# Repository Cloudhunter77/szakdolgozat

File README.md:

# ModuNode – moduláris okosotthon platform

Szakdolgozat: moduláris okosotthon node-ok ESP32-C6 mikrovezérlőn. A végleges irány Matter (over Thread)
Home Assistanttal; a köztes lépések ESPHome-on készültek.

## Szerkezet
| Mappa | Tartalom | Állapot |
|---|---|---|
| [`firmware/esphome-demo/`](firmware/esphome-demo/) | ESPHome vezérlő demó: relé, ajtóérzékelő, Kézi/Automata mód, webes felület | ✅ hardveren tesztelve |
| [`firmware/matter-c6/`](firmware/matter-c6/) | ESP-Matter alapú firmware, Matter over Thread, Home Assistant | ✅ párosítva HA-ba (cp-02) |
| [`docs/`](docs/) | Tervek, jegyzetek | |

A tesztelt, visszaállítható állapotok listája: [`CHECKPOINTS.md`](CHECKPOINTS.md).

## Eszközök
- Hardver: ESP32-C6 (DevKitC-1 / Super Mini), Home Assistant + Thread border router
- ESPHome (Python venv), ESP-IDF v5.5.5 + `espressif/esp_matter` komponens
- Fejlesztői gép: Linux Mint

Az egyes alprojektek indítása a saját `README.md`-jükben van.

## Titkok
A WiFi jelszavak és kulcsok a `secrets.yaml` fájlokban vannak, ezek **nincsenek** a repóban.
Új gépen a `secrets.example.yaml`-ből kell létrehozni őket.

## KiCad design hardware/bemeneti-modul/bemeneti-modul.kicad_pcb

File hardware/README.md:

# Hardver – KiCad 10 projektek

Specifikációk: `docs/kontextus/MODULMAG-SPEC.md`, `docs/kontextus/VEZERLO-SPEC.md`; ütemterv: `docs/kontextus/UTEMTERV.md`.

| Mappa | Mi |
|---|---|
| `lib/` | közös saját könyvtár: `modularis.kicad_sym`, `modularis.pretty/`, `3d/` |
| `modulmag/` | a modulmag **egyetlen** kapcsolási lapja; a három modul hierarchikus lapként használja (`../modulmag/modulmag.kicad_sch`), a saját projektje csak az önálló ellenőrzéshez kell |
| `vezerlo/` | ESP32-C6 vezérlő |
| `led-modul/`, `rele-modul/`, `bemeneti-modul/` | a modulok (modulmag + a saját részük) |
| `gen/` | a vázlatok generátora: `gen/build.sh <lap>` → `<lap>.py` → `.kicad_sch` + ERC, netlista, PDF az `out/`-ba. **Felülírja a kézi elrendezést** – elrendezés után már csak kézzel módosítsd a lapot |

Laponként külön projekt = külön NYÁK, külön gerber. A modulmagot csak egy helyen kell javítani.

Ellenőrzés (Claude Code futtatja): `kicad-cli` (Flatpak: `flatpak run --command=kicad-cli org.kicad.KiCad`) –
ERC, netlista-export és összevetés a specifikációval, később DRC és gerber.

## Munkafolyamat (D67)

- **Forrás:** amíg Balázs egy lapot nem szerkeszt kézzel, a `gen/<lap>.py` a forrás. Amint kézzel átrendez rajta
  valamit, onnantól a `.kicad_sch` – arra a lapra a generátort **nem futtatjuk újra** (a mozgatások elvesznének).
  A kézzel átvett lapok: **mind az öt (2026-10-23)** – `gen/kezi-lapok.txt`; a `build.sh` ezeket nem generálja újra, csak
  ellenőrzi (ERC, netlista, PDF). Módosítás innentől a `.kicad_sch`-ban (KiCad-ben vagy MCP-vel), nem a `gen/<lap>.py`-ban.
- **Egyszerre csak egyikünk szerkeszt:** Balázs ment → Claude módosít (fájlban vagy KiCad MCP-vel) → Balázs a
  KiCad-ben újratölti a lapot (File → Revert).
- **Minden módosítás után:**
  - `gen/build.sh <lap>` (csak generátoros lapnál) – ERC-t is futtat, `Found 0 violations` kell
    (a `modulmag` önállóan ~55 jelzést ad a lógó hierarchikus lábak miatt – ez rendben van, a modulok ERC-je a mérvadó)
  - netlista-összevetés: `kicad-cli sch export netlist -o out/<lap>.net <lap>/<lap>.kicad_sch`, majd
    `python3 -I gen/netcmp.py out/<lap>.before.net out/<lap>.net` – a bekötés változatlan, ha 0 / 0 eltérés
    (relé és LED: 4 várt eltérés a D6/JP2 buszos táp opció miatt). Az `out/` gitignore-ban van, a `.before.net`
    csak helyben létezik; szándékos bekötés-változás után újra kell menteni.
  - vizuális ellenőrzés: KiCad MCP `sch_visual_qa` – a „symbol_overlap” többnyire formai (tápszimbólum a láb végén,
    szomszédos alkatrész, többegységes U9), ezért PDF → PNG kivágáson is megnézni.
- **KiCad MCP:** `kicad-mcp-pro` (uvx, Python 3.13), helyi scope, munkaterület = `hardware/`, **írható mód**
  (`KICAD_MCP_OPERATING_MODE=write`). Minden projektmappában `output/` munkamappát hoz létre (gitignore-ban).

**Fő áramutak (`gen/aramut.py`, D91):** `flatpak run --command=python3 org.kicad.KiCad gen/aramut.py <lap>` – a DRC-ben a táp-sávok
minimuma csak 0,2 mm (mellékágak), ezért ez nézi, hogy a fő út (pl. betáp → biztosíték → sorkapocs, FET → sönt, busz) a keskenyebb
sávok nélkül is egyben van-e; az `ellenorzes.py` 6. lépése futtatja.

**Rajzszerkesztés szkriptből (`gen/schedit.py`, D90):** a kézi `.kicad_sch`-okhoz – szimbólumok és lábpozíciók (a forgatás /
tükrözés a `kigen` szerint), vezeték, címke, tápszimbólum (a hálózat neve a Value), PWR_FLAG, törlés, áthelyezés, címke csonkra
(`stub_labels`), a D-hivatkozások kivétele a konzulensnek szánt szövegekből (`strip_d`). A `save()` csak akkor ír, ha a fájl a beolvasás
óta nem változott (Balázs nem mentett közben). Minden módosítás után: netlista-összevetés (`gen/netcmp.py`) + ERC + SVG-kép.

## STM32CubeMX-projektek (`cubemx/`)
`python3 gen/cubemx.py` → `cubemx/<modul>/<modul>.ioc` a MODULMAG-SPEC 7. fejezetének lábkiosztásából (a jel- és
üzemmódnevek a CubeMX 6.18 adatbázisából). MCU: **STM32L433RCT3** (D78). Indítás: `flatpak run com.st.STM32CubeMX` →
File → Load Project. A pinout nézet a lábhozzárendelést ellenőrzi; a belső kapcsolatokat (COMP2 → TIM1/TIM15/TIM16 BKIN,
DAC1_OUT1 → COMP2 INM, ADC1_IN8 + COMP2_INP a PA3-on) a CubeMX-ben kézzel kell beállítani és megnézni.

## Teljes ellenőrzés (`gen/ellenorzes.py`, 2026-10-22)
`python3 gen/ellenorzes.py` (a `hardware/` mappából) – minden lapot újragenerál és ellenőriz:
1. ERC (elfogadott: a modulmag önálló hierarchikus jelzései, a relén a 4 lib-jelzés);
2. minden bekötött szimbólumláb létezik-e a footprinten (láb ↔ pad);
3. a modulmag bekötése mindhárom modulban (L433 táplábak, SN65HVD230, AP2112K, táp-LED, BOOT0, busz-GND);
4. a CubeMX-projekt címkéi ↔ a rajz hálózatai ↔ az L433-adatbázis (rendelhető-e a jel a lábhoz); 4b. a CubeMX
   fejsorból betölti az .ioc-kat és kódot generál (`out/cubemx-test/`) – minden periféria inicializálódik-e;
5. a GND-ági polaritásvédő FET-ek (D78) bekötése;
6. NYÁK ↔ rajz (alkatrészek, padok hálózatai, footprintek, szimbólum-kapcsolat), 1 oz-os rétegrend (D82), tiltott területek, DRC;
7. elavult kifejezések a generátorokban és a dokumentációban (csak figyelmeztetés).
Kapcsolók: `--no-build` (a meglévő netlistákból), `--no-cubemx`. „HIBA” = javítandó; a szitanyomat-jelzések a
layoutnál rendeződnek (figyelmeztetés). Kilépési kód 1, ha van hiba.

**NYÁK-módosítás szkriptből (2026-11-02):** a KiCad Pythonjának `SaveBoard`-ja a `.kicad_pro`-t is újraírja, és ilyenkor kiesnek
belőle a kapcsolási rajz beállításai, valamint a sáv- és via-előbeállítások. Utána: `git restore <lap>/<lap>.kicad_pro`.
A zónákat **ne** a Pythonban töltsd ki, mert az nem olvassa a `.kicad_dru` szabályait (pl. a 0,8 mm-es leválasztást), hanem így:
`kicad-cli pcb drc --refill-zones --save-board …` (vagy KiCad-ben: B). Előtte nézd meg, hogy Balázs mentett-e (mtime), utána nála
File → Revert.

**UUID-k (10-22):** a generátor determinisztikus – a szimbólumok UUID-je a projekt + hivatkozási jel alapján képződik, így
újragenerálás után is egyezik a NYÁK footprintjeinek útvonalával („Update PCB from Schematic” működik); a többi elem UUID-je
laponként sorszámból képződik (két futás bájtra azonos fájlt ad).

## Konzulensi PDF (`gen/pdf.sh`)
`bash gen/pdf.sh` → `out/kapcsolasi-rajzok-<dátum>.pdf` – a mostani `.kicad_sch`-okból (a rajzokhoz nem nyúl), minden lap egyszer,
a komponenslista sorrendjében: vezérlő, modulmag, LED-, relé-, bemeneti modul (5 oldal).

## Darabjegyzék (`gen/bom.sh`)
`bash gen/bom.sh` → `bom/<lap>.csv` – laponként, értékenként és footprintenként csoportosítva, a DNP-k nélkül
(a „Megjegyzés” mezővel). A kézben lévő és a megveendő tételek: `docs/kontextus/SAMPLE-KERESEK.md`.

**Beszerzési lista (`gen/beszerzes.py`, D85):** `python3 gen/beszerzes.py [--frissit]` → `bom/beszerzes.csv` (a négy BOM
összesítve, soronként a legolcsóbb forrás ÁFA-val: Hestore – a termékoldalról – vagy LCSC – a JLC alkatrészkeresőjéből,
`gen/lcsc.py`) és `bom/lcsc-kosar.csv` (az LCSC BOM Tooljába feltölthető: kód, darab). A forrás-hozzárendelés a `FORRAS`
táblában van (ellenállás / kondenzátor magától); ha a BOM-ba ismeretlen tétel kerül, „HIBA”. Gyorsítótár: `out/hestore/`, `out/lcsc/`.

## NYÁK-előkészítés (2026-10-21, D73)
`gen/pcbgen.py` a netlistából (`out/<lap>.net`) elkészíti a `<lap>/<lap>.kicad_pcb`-t: 4 réteg, körvonal (86,5 × 68 mm;
a bemeneti modul 86,5 × 103 mm), DIN-zónák a Dwgs.User rétegen (felső/alsó váll, előlapi ablak), a footprintek a
hálózatokkal és a kapcsolási rajzhoz kötve (az „Update PCB from Schematic” működik; a DNP-jelző és a mezők is átkerülnek – D89), kezdő elhelyezés: a csatlakozók
a ház szerinti élen, a többi a hozzá kötött IC köré. Huzalozás nincs – azt kézzel.

    flatpak run --command=python3 org.kicad.KiCad gen/pcbgen.py <lap> [--force]   # board generálása
    gen/pcbshow.sh <lap> kep.png                                                  # kép ellenőrzéshez

**Szabályok (D86):** laponként `<lap>/<lap>.kicad_dru` – JLC 4 réteg / 1 oz, via 0,3 / 0,45 (jel), 0,4 / 0,7 (táp), 0,6 / 1,0 mm
(nagyáram), 230 V-os távolságok; a KiCad magától betölti (Board Setup → Custom Rules). **Modulmag-blokk:** a `pcbgen.py`
`MODULMAG_BLOKK` sablonja mindhárom modulon azonos relatív elrendezést ad (a lap `blokk=(x, y)` eltolásával).

**Vezérlő (D87):** az U4 a jobb élen (antenna kifelé), a két buck rögzített relatív elrendezéssel (`VEZ_U1`, `VEZ_U2` – TI-ajánlás);
a kisebb alkatrészek a `pin_attach` szerint a saját lábukhoz (a felhúzó a jellábhoz, több azonos tápú lábnál sorban mindegyikhez).

**A D67 a NYÁK-ra is érvényes:** amint egy `.kicad_pcb`-t kézzel szerkesztettél, az a forrás; a szkript csak
`--force`-szal írja felül. Kapcsolási rajz változása után a KiCad-ben: *Tools → Update PCB from Schematic*. **Kézi NYÁK-ok:** led-modul (Balázs huzalozza, 2026-10-23).

**Szitanyomat-feliratok (`gen/felirat.py`):** `flatpak run --command=python3 org.kicad.KiCad gen/felirat.py <be> <ki>` – minden
jelölést a saját alkatrésze mellé tesz (0°/90°, 1,0 mm, ahol nem fér el 0,8 mm), padra, viára, furatra, ≥ 1 mm-es (fedetlen, D82) sávra
és más feliratra nem lóghat, a szitanyomat-rajzokat (a lapra rajzoltakat is) kerüli; ami 4 mm-en belül nem fér el, azt 6–8 mm-es körzetben
keresi. Csak a feliratokhoz nyúl. Kézi NYÁK-on: Balázs ment → futtatás → a KiCad-ben File → Revert.
`--csak R1,C2,…`: csak ezek felirata mozdul, a többi (kézzel igazított) felirat akadály.

**Maszknyitás a nagyáramú utakon (`gen/maszknyitas.py`, D82):** `flatpak run --command=python3 org.kicad.KiCad gen/maszknyitas.py <be> <ki>`
– a nagyáramú hálózatok ≥ 1 mm-es sávjai és külső zónái fölé kitöltött sokszöget tesz az F.Mask / B.Mask rétegre (ónnal / rézdróttal
megvastagításhoz); felül az alkatrészek udvara és a sönt (R209) 1,5 mm-es környéke fedett marad. A „D82 maszknyitás” csoportba kerül,
újrafuttatva lecseréli – huzalozás-módosítás után: zónatöltés (B) → mentés → futtatás → File → Revert. A hálózatok: `--halok REGEX`
(alapból a LED-modulé), a sönt: `--sont R209`. A `felirat.py` a nyitásokat is kerüli.

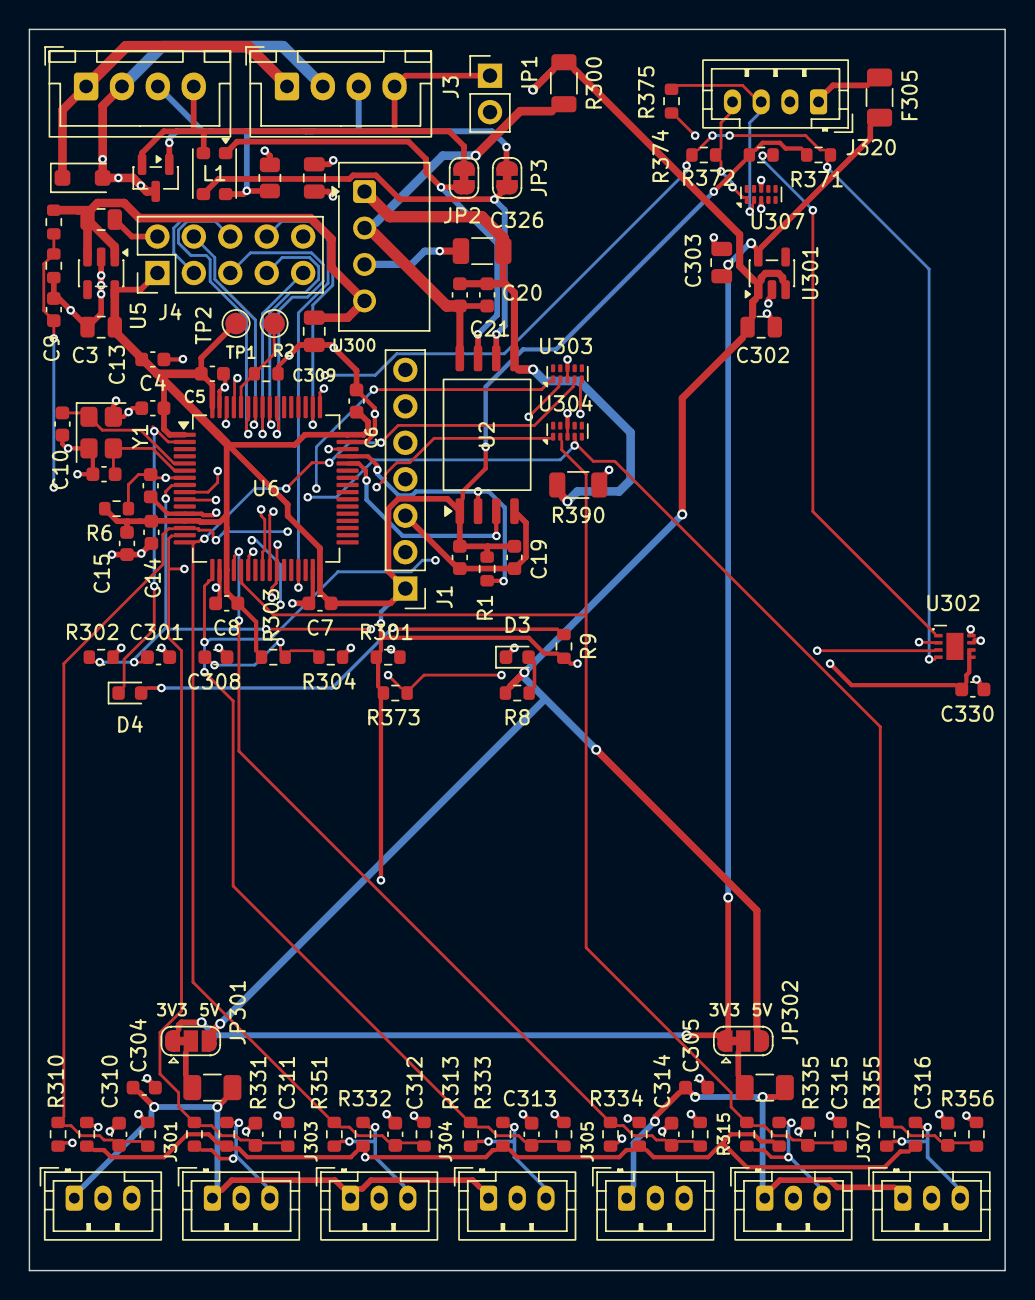
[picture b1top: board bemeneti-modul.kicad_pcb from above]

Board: 4 copper layers, 68.0 x 86.5 mm, 112 parts (0 on the bottom side), 58 nets.

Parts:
C2, C3, C303, C309: 10µ; C_0805_2012Metric
C4, C5, C6, C7, C8, C9, C16, C18, C20, C301, C308, C330: 100n; C_0603_1608Metric
C10, C11: 12p; C_0603_1608Metric
C13, C19, C21: 4µ7; C_0603_1608Metric
C14, C304, C305: 1µ; C_0603_1608Metric
C15, C310, C311, C312, C313, C314, C315, C316: 10n; C_0603_1608Metric
C300: 4µ7; C_0805_2012Metric
C302: 10µ/10V; C_0805_2012Metric
C326: 2n2/1kV; C_1206_3216Metric
D3: zöld; LED_0603_1608Metric
D4: piros; LED_0603_1608Metric
D5: SMF5.0A; D_SOD-123F
F301, F302, F305: PTC 0,2A; Fuse_1206_3216Metric
J1: DEBUG; PinHeader_1x07_P2.54mm_Vertical
J2: BUS_IN; JST_XH_B4B-XH-A_1x04_P2.50mm_Vertical
J3: BUS_OUT; JST_XH_B4B-XH-A_1x04_P2.50mm_Vertical
J4: BŐVÍTŐ; PinHeader_2x05_P2.54mm_Vertical
J301: IN0; JST_PH_B3B-PH-K_1x03_P2.00mm_Vertical
J302: IN1; JST_PH_B3B-PH-K_1x03_P2.00mm_Vertical
J303: IN2; JST_PH_B3B-PH-K_1x03_P2.00mm_Vertical
J304: IN3; JST_PH_B3B-PH-K_1x03_P2.00mm_Vertical
J305: IN4; JST_PH_B3B-PH-K_1x03_P2.00mm_Vertical
J306: IN5; JST_PH_B3B-PH-K_1x03_P2.00mm_Vertical
J307: IN6; JST_PH_B3B-PH-K_1x03_P2.00mm_Vertical
J320: I2C KÜLSŐ; JST_PH_B4B-PH-K_1x04_P2.00mm_Vertical
JP1: LEZÁRÁS; PinHeader_1x02_P2.54mm_Vertical
JP2, JP3: áthidaló; SolderJumper-2_P1.3mm_Bridged_RoundedPad1.0x1.5mm
JP301: CSOPORT 1; SolderJumper-3_P1.3mm_Bridged12_RoundedPad1.0x1.5mm
JP302: CSOPORT 2; SolderJumper-3_P1.3mm_Bridged12_RoundedPad1.0x1.5mm
L1: DNP; L_CommonModeChoke_Coilank_ACM3225
R1, R2, R6, R310, R311, R312, R313, R314, R315, R316, R330, R331, R332, R333, R334, R335, R336, R373: 10k; R_0603_1608Metric
R3, R4, R301, R303: 10k 1%; R_0603_1608Metric
R5: 120R; R_0805_2012Metric
R8: 2k2; R_0603_1608Metric
R9: 1k; R_0603_1608Metric
R300, R390: 0R; R_1206_3216Metric
R302: 2k49 1%; R_0603_1608Metric
R304: 715R 1%; R_0603_1608Metric
R350, R351, R352, R353, R354, R355, R356: DNP; R_0603_1608Metric
R371, R372: 4k7; R_0603_1608Metric
R374, R375: 100R; R_0603_1608Metric
TP1: BOOT0; TestPoint_Pad_D1.5mm
TP2: 3V3; TestPoint_Pad_D1.5mm
U2: CA-IS3052G; SOIC-8_7.5x5.85mm_P1.27mm
U3: ESD2CAN24-Q1; SOT-23
U5, U301: AP2112K-3.3TRG1; SOT-23-5
U6: STM32L433RCT3; LQFP-64_10x10mm_P0.5mm
U300: B0505S-1WR3; Converter_DCDC_TRACO_TME_03xxS_05xxS_12xxS_Single_THT
U302: HDC3020DEFR; TI_WSON-8-1EP_2.5x2.5mm_DEF0008A
U303, U304, U307: TPD4E05U06DQAR; USON-10_2.5x1.0mm_P0.5mm
Y1: 8MHz; Crystal_SMD_3225-4Pin_3.2x2.5mm

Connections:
+3V3: C3.1, C4.1, C5.1, C6.1, C7.1, C8.1, C13.1, C14.1, C15.1, C18.1, C19.1, C330.1, J1.1, J4.1, R1.1, R6.1, R9.1, R301.1, R303.1, R330.1, R331.1, R332.1, R333.1, R334.1, R335.1, R336.1, R371.1, R372.1, R373.1, TP2.1, U2.1, U5.5, U6.1, U6.13, U6.19, U6.32, U6.48, U6.64, U302.5, U302.6
+3V3S: C303.1, F305.1, JP301.1, JP302.1, U301.5
+5V: C2.1, C302.1, C309.1, JP301.3, JP302.3, R3.1, R8.1, R300.2, U5.1, U5.3, U300.4, U301.1, U301.3
/GND_BUS: C20.2, C21.2, C300.2, C326.1, D5.2, J2.2, J3.2, R390.1, U2.5, U3.3, U300.1
/HDC_ALERT: R373.2, U6.10, U302.3
/HW_ID: C301.1, R301.2, R302.1, U6.8
/HW_REV: C308.1, R303.2, R304.1, U6.26
/I2C_SCL: R371.2, R374.1, U6.61, U302.4
/I2C_SDA: R372.2, R375.1, U6.62, U302.1
/IN0: C310.1, R310.2, R350.1, U6.14, U303.1
/IN1: C311.1, R311.2, R351.1, U6.15, U303.2
/IN2: C312.1, R312.2, R352.1, U6.16, U303.4
/IN3: C313.1, R313.2, R353.1, U6.17, U303.5
/IN4: C314.1, R314.2, R354.1, U6.20, U304.1
/IN5: C315.1, R315.2, R355.1, U6.21, U304.2
/IN6: C316.1, R316.2, R356.1, U6.22, U304.4
/SCL_EXT: J320.4, R374.2, U307.1
/SDA_EXT: J320.3, R375.2, U307.2
/modulmag/BOOT0: R2.1, TP1.1, U6.60
/modulmag/CAN_H: J2.4, J3.4, JP1.1, JP2.2, L1.2, U3.2
/modulmag/CAN_H_T: JP2.1, L1.1, U2.7
/modulmag/CAN_L: J2.3, J3.3, JP3.2, L1.4, R5.2, U3.1
/modulmag/CAN_L_T: JP3.1, L1.3, U2.6
/modulmag/CAN_RX: U2.3, U6.44
/modulmag/CAN_TX: R1.2, U2.2, U6.45
/modulmag/EXP_PA15: J4.3, U6.50
/modulmag/EXP_PB3: J4.5, U6.55
/modulmag/EXP_PB4: J4.7, U6.56
/modulmag/EXP_PB5: J4.9, U6.57
/modulmag/EXP_PB6: J4.4, U6.58
/modulmag/EXP_PB7: J4.6, U6.59
/modulmag/EXP_PB10: J4.8, U6.29
/modulmag/NRST: C16.1, J1.5, R6.2, U6.7
/modulmag/OSC_IN: C10.1, U6.5, Y1.1
/modulmag/OSC_OUT: C11.1, U6.6, Y1.3
/modulmag/STATUS_LED: D4.1, U6.2
/modulmag/SWCLK: J1.2, U6.49
/modulmag/SWDIO: J1.4, U6.46
/modulmag/UART_RX: J1.7, U6.25
/modulmag/UART_TX: J1.6, U6.24
/modulmag/VBUS_SENSE: C9.1, R3.2, R4.1, U6.9
GND: C2.2, C3.2, C4.2, C5.2, C6.2, C7.2, C8.2, C9.2, C10.2, C11.2, C13.2, C14.2, C15.2, C16.2, C18.2, C19.2, C301.2, C302.2, C303.2, C304.2, C305.2, C308.2, C309.2, C310.2, C311.2, C312.2, C313.2, C314.2, C315.2, C316.2, C326.2, C330.2, D3.1, J1.3, J4.2, J4.10, J301.2, J302.2, J303.2, J304.2, J305.2, J306.2, J307.2, J320.2, R2.2, R4.2, R302.2, R304.2, R350.2, R351.2, R352.2, R353.2, R354.2, R355.2, R356.2, R390.2, U2.4, U5.2, U6.12, U6.18, U6.31, U6.47, U6.63, U300.3, U301.2, U302.2, U302.7, U302.8, U303.3, U303.8, U304.3, U304.8, U307.3, U307.8, Y1.2, Y1.4
unnamed: D3.2, R8.2
unnamed: D4.2, R9.2
unnamed: J301.3, R310.1, R330.2
unnamed: J302.3, R311.1, R331.2
unnamed: J303.3, R312.1, R332.2
unnamed: J304.3, R313.1, R333.2
unnamed: J305.3, R314.1, R334.2
unnamed: J306.3, R315.1, R335.2
unnamed: J307.3, R316.1, R336.2
unnamed: JP1.2, R5.1
unnamed: F301.1, JP301.2
unnamed: F302.1, JP302.2
SUP1: C304.1, F301.2, J301.1, J302.1, J303.1, J304.1
SUP2: C305.1, F302.2, J305.1, J306.1, J307.1
SUP_I2C: F305.2, J320.1
V_BUS: C20.1, C21.1, C300.1, D5.1, J2.1, J3.1, R300.1, U2.8, U300.2

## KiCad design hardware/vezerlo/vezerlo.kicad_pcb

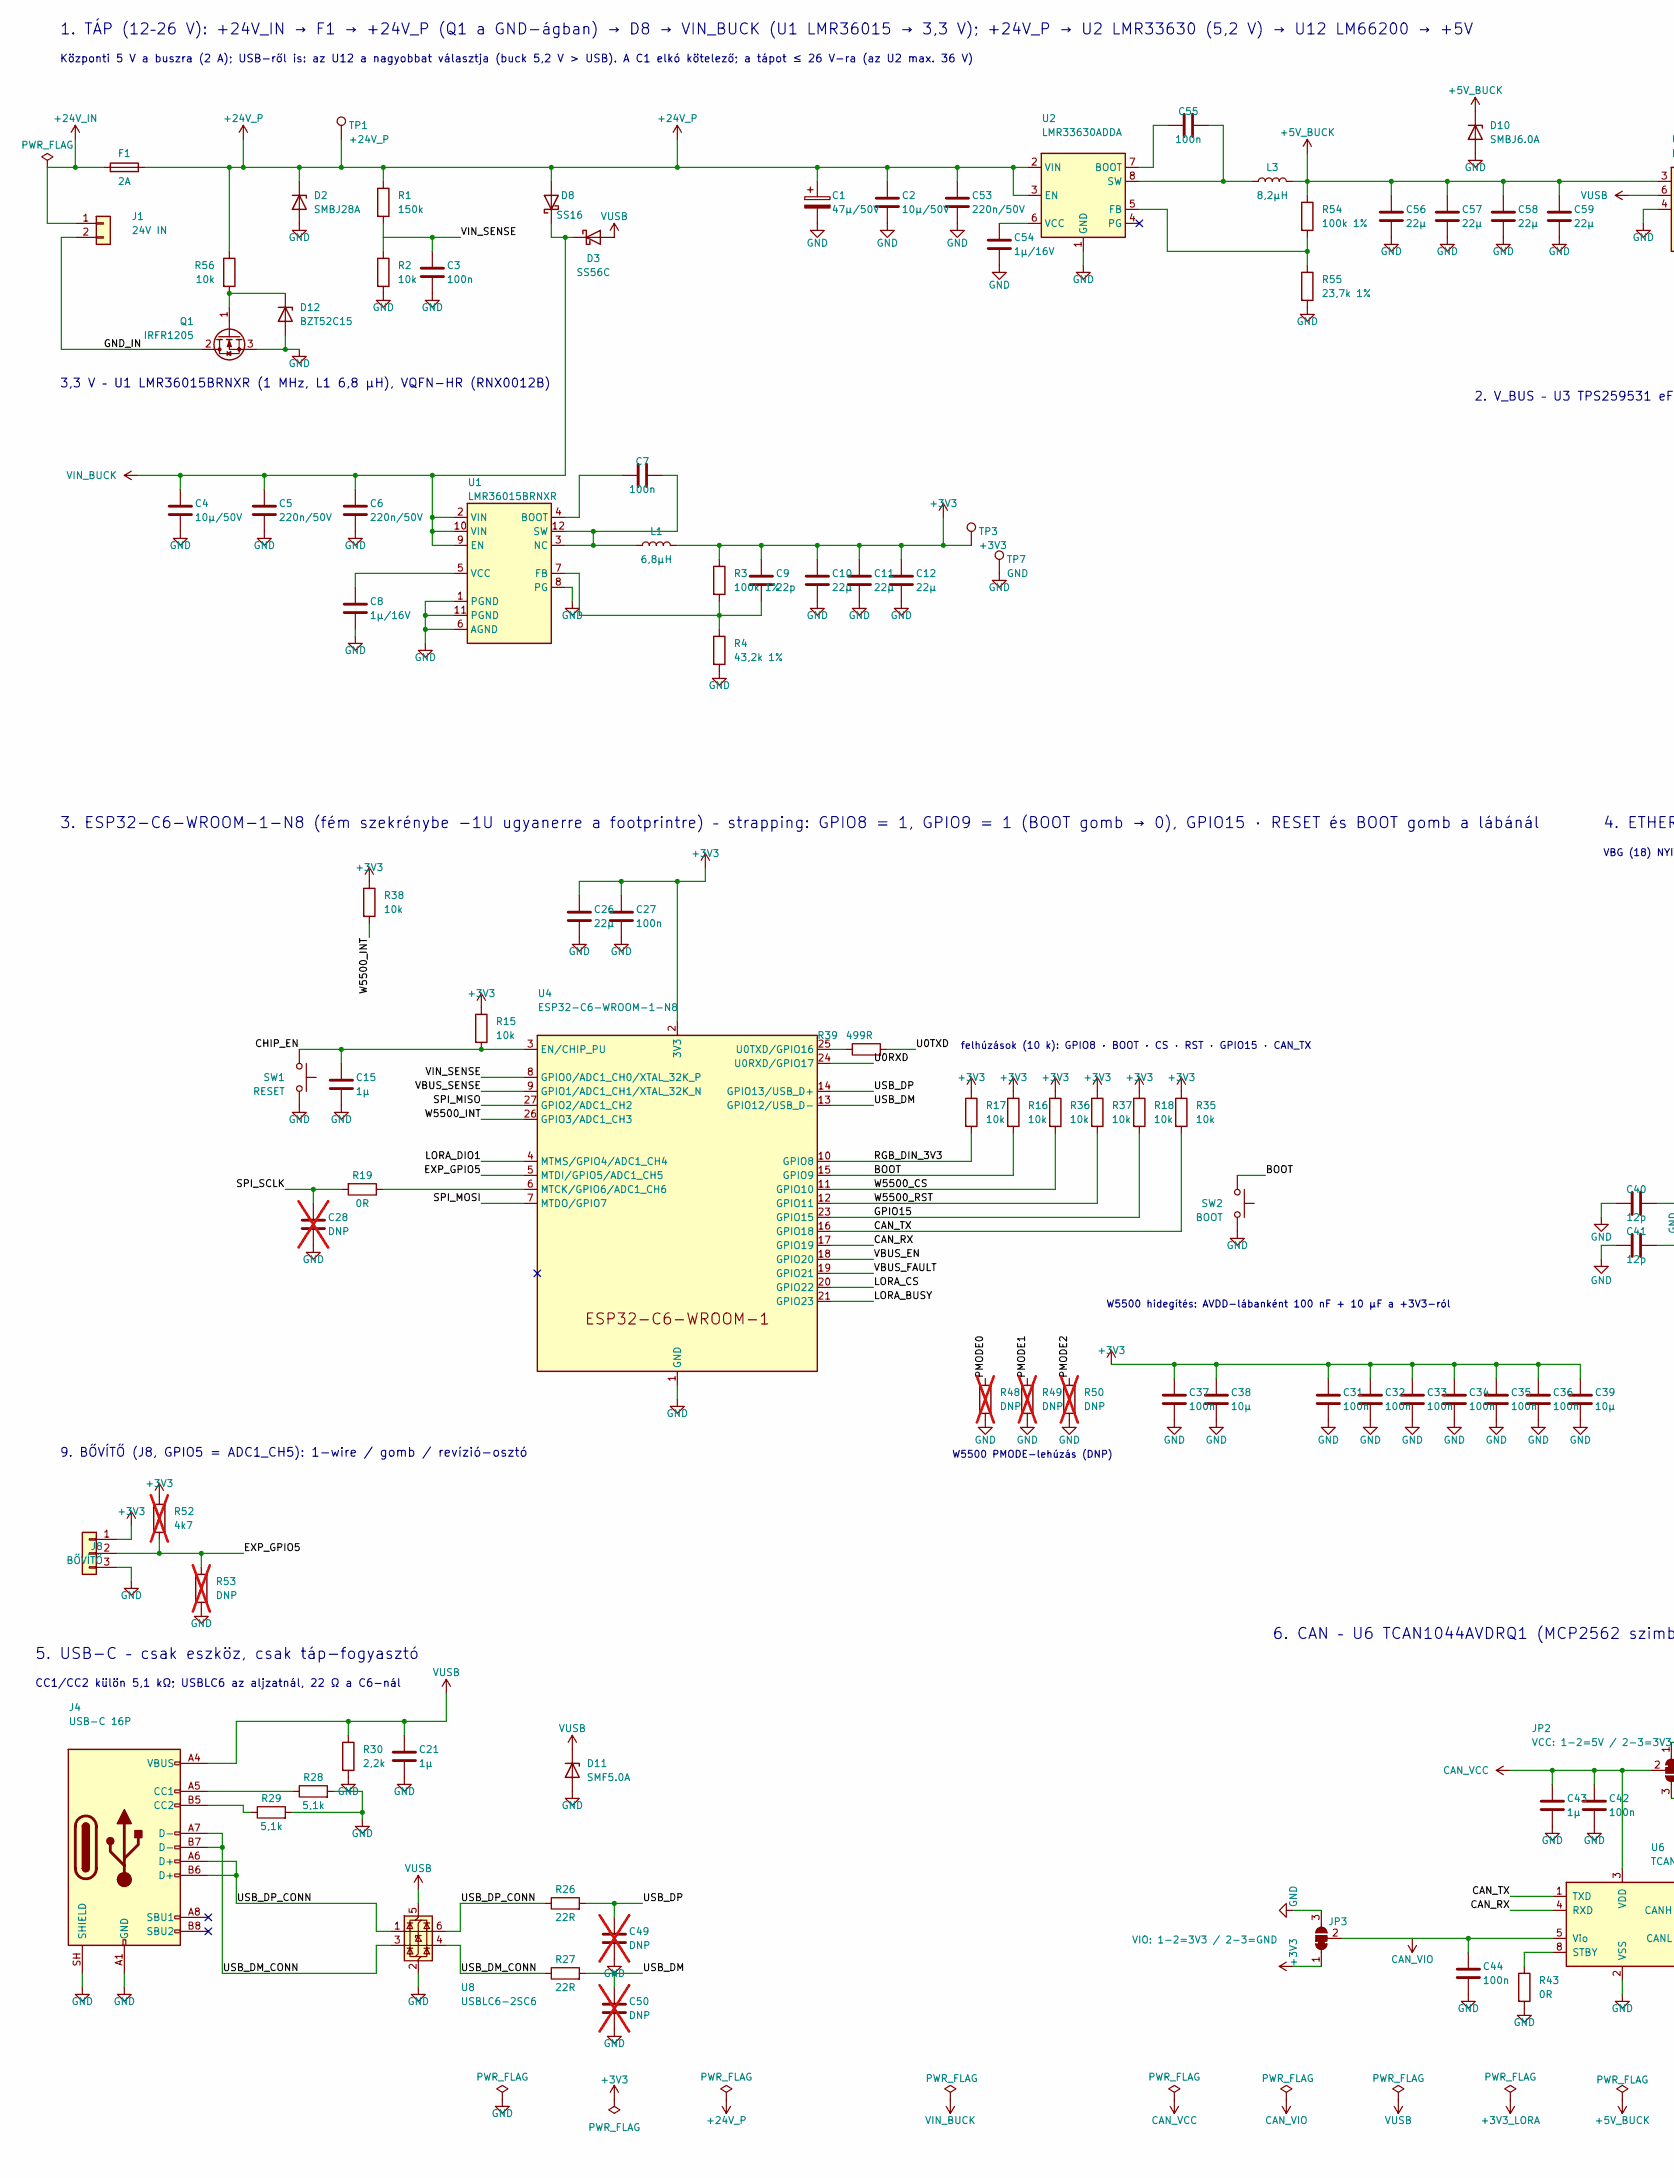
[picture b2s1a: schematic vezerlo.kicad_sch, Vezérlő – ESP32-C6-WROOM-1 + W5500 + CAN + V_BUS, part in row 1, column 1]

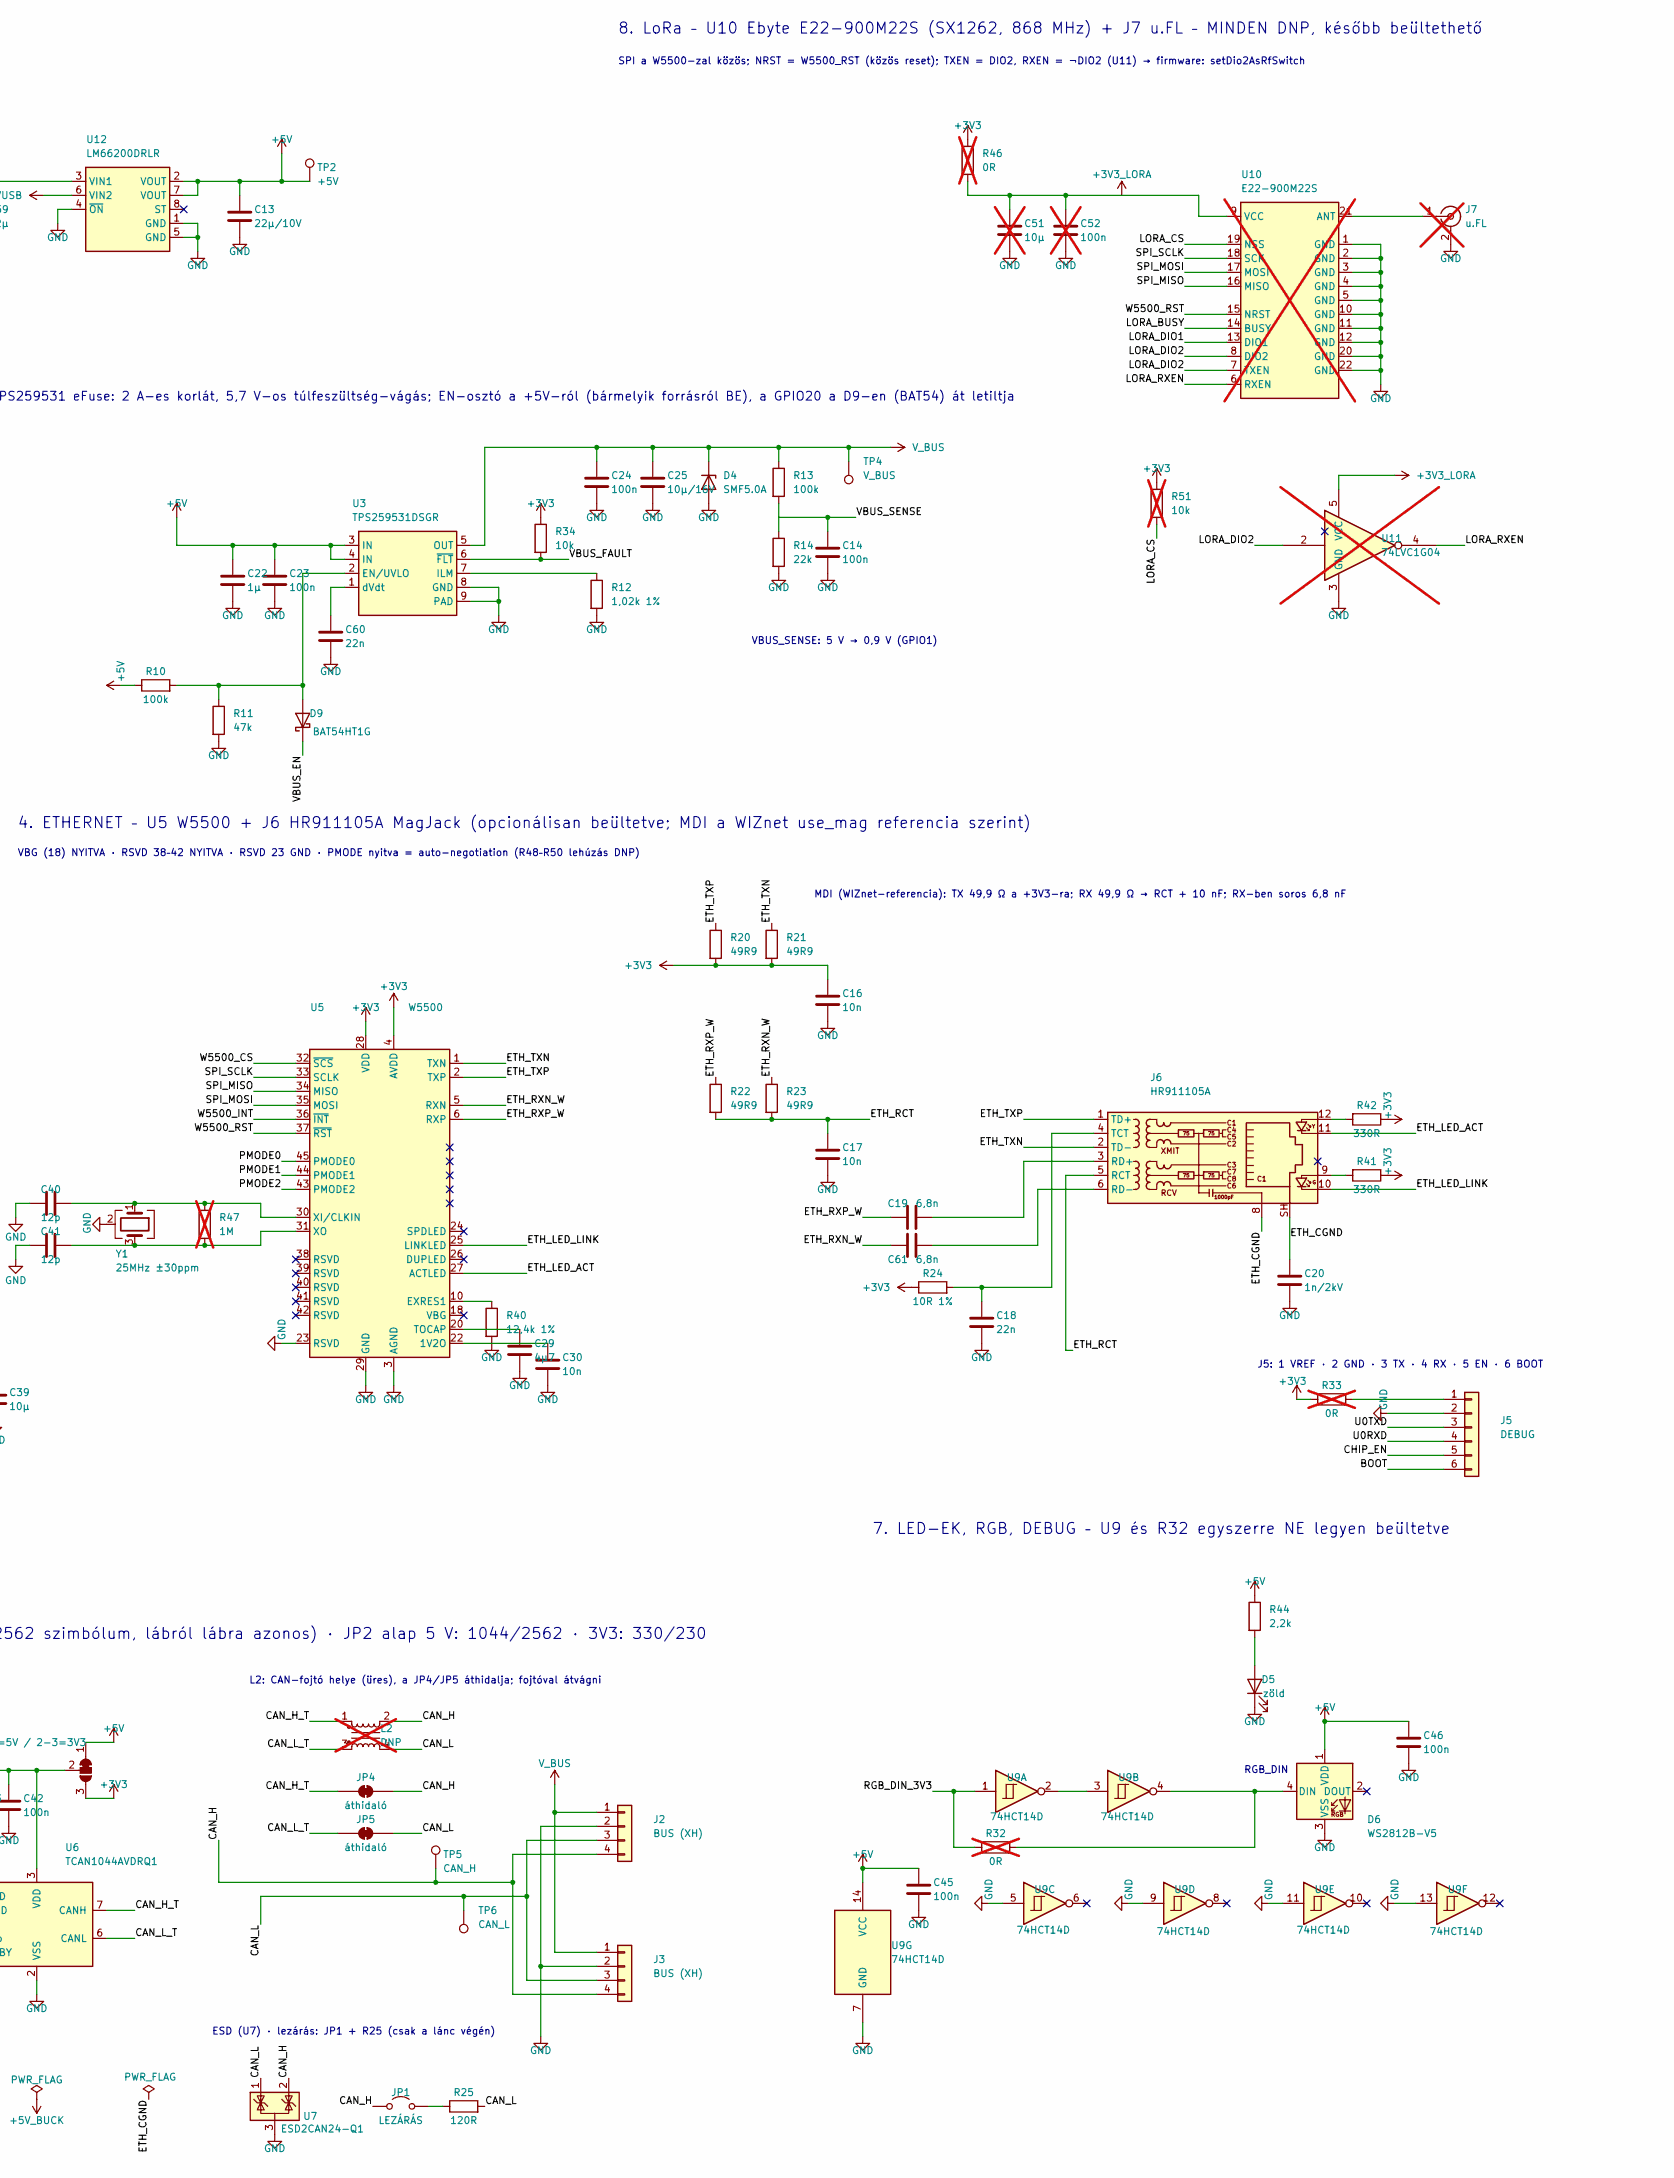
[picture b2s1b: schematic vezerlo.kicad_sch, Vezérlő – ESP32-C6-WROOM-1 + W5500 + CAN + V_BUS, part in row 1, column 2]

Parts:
C1: 47µ/50V; CP_Elec_6.3x7.7
C2, C4: 10µ/50V; C_1210_3225Metric
C3, C7, C14, C23, C24, C27, C31, C32, C33, C34, C35, C36, C37, C42, C44, C45, C46, C55: 100n; C_0603_1608Metric
C5, C6, C53: 220n/50V; C_0603_1608Metric
C8, C54: 1µ/16V; C_0603_1608Metric
C9: 22p; C_0603_1608Metric
C10, C11, C12, C56, C57, C58, C59: 22µ; C_1206_3216Metric
C13: 22µ/10V; C_1206_3216Metric
C15, C21, C22, C43: 1µ; C_0603_1608Metric
C16, C17, C30: 10n; C_0603_1608Metric
C18, C60: 22n; C_0603_1608Metric
C19, C61: 6,8n; C_0603_1608Metric
C20: 1n/2kV; C_1206_3216Metric
C25: 10µ/16V; C_0805_2012Metric
C26: 22µ; C_0805_2012Metric
C28, C49, C50: DNP; C_0603_1608Metric; not fitted
C29: 4µ7; C_0805_2012Metric
C38, C39: 10µ; C_0805_2012Metric
C40, C41: 12p; C_0603_1608Metric
C51: 10µ; C_0805_2012Metric; not fitted
C52: 100n; C_0603_1608Metric; not fitted
D2: SMBJ28A; D_SMB
D3: SS56C; D_SMC
D4, D11: SMF5.0A; D_SOD-123F
D5: zöld; LED_0603_1608Metric
D6: WS2812B-V5; LED_WS2812B_PLCC4_5.0x5.0mm_P3.2mm
D8: SS16; D_SMA
D9: BAT54HT1G; D_SOD-323
D10: SMBJ6.0A; D_SMB
D12: BZT52C15; D_SOD-123
F1: 2A; Fuse_1206_3216Metric
J1: 24V IN; TerminalBlock_Phoenix_MKDS-1,5-2_1x02_P5.00mm_Horizontal
J2, J3: BUS (XH); JST_XH_B4B-XH-A_1x04_P2.50mm_Vertical
J4: USB-C 16P; USB_C_Receptacle_HRO_TYPE-C-31-M-12
J5: DEBUG; PinHeader_1x06_P2.54mm_Vertical
J6: HR911105A; RJ45_Hanrun_HR911105A_Horizontal
J7: u.FL; U.FL_Hirose_U.FL-R-SMT-1_Vertical; not fitted
J8: BŐVÍTŐ; JST_PH_B3B-PH-K_1x03_P2.00mm_Vertical
JP1: LEZÁRÁS; PinHeader_1x02_P2.54mm_Vertical
JP2: VCC: 1-2=5V / 2-3=3V3; SolderJumper-3_P1.3mm_Bridged12_RoundedPad1.0x1.5mm
JP3: VIO: 1-2=3V3 / 2-3=GND; SolderJumper-3_P1.3mm_Bridged12_RoundedPad1.0x1.5mm
JP4, JP5: áthidaló; SolderJumper-2_P1.3mm_Bridged_RoundedPad1.0x1.5mm
L1: 6,8µH; L_FerroCore_HPI0630
L2: DNP; L_CommonModeChoke_Coilank_ACM3225; not fitted
L3: 8,2µH; L_FerroCore_HPI0630
Q1: IRFR1205; TO-252-2
R1: 150k; R_0603_1608Metric
R2, R15, R16, R17, R18, R34, R35, R36, R37, R38, R56: 10k; R_0603_1608Metric
R3, R54: 100k 1%; R_0603_1608Metric
R4: 43,2k 1%; R_0603_1608Metric
R10, R13: 100k; R_0603_1608Metric
R11: 47k; R_0603_1608Metric
R12: 1,02k 1%; R_0603_1608Metric
R14: 22k; R_0603_1608Metric
R19, R43: 0R; R_0603_1608Metric
R20, R21, R22, R23: 49R9; R_0603_1608Metric
R24: 10R 1%; R_0603_1608Metric
R25: 120R; R_0805_2012Metric
R26, R27: 22R; R_0603_1608Metric
R28, R29: 5,1k; R_0603_1608Metric
R30, R44: 2,2k; R_0603_1608Metric
R32, R33, R46: 0R; R_0603_1608Metric; not fitted
R39: 499R; R_0603_1608Metric
R40: 12,4k 1%; R_0603_1608Metric
R41, R42: 330R; R_0603_1608Metric
R47: 1M; R_0603_1608Metric; not fitted
R48, R49, R50, R53: DNP; R_0603_1608Metric; not fitted
R51: 10k; R_0603_1608Metric; not fitted
R52: 4k7; R_0603_1608Metric; not fitted
R55: 23,7k 1%; R_0603_1608Metric
SW1: RESET; SW_SPST_TL3342
SW2: BOOT; SW_SPST_TL3342
TP1: +24V_P; TestPoint_Pad_D1.5mm
TP2: +5V; TestPoint_Pad_D1.5mm
TP3: +3V3; TestPoint_Pad_D1.5mm
TP4: V_BUS; TestPoint_Pad_D1.5mm
TP5: CAN_H; TestPoint_Pad_D1.5mm
TP6: CAN_L; TestPoint_Pad_D1.5mm
TP7: GND; TestPoint_Pad_D1.5mm
U1: LMR36015BRNXR; TI_VQFN-HR-12_RNX0012B
U2: LMR33630ADDA; Texas_HSOP-8-1EP_3.9x4.9mm_P1.27mm_ThermalVias
U3: TPS259531DSGR; Texas_DSG0008A_WSON-8-1EP_2x2mm_P0.5mm_EP0.9x1.6mm
U4: ESP32-C6-WROOM-1-N8; ESP32-C6-WROOM-1
U5: W5500; LQFP-48_7x7mm_P0.5mm
U6: TCAN1044AVDRQ1; SOIC-8_3.9x4.9mm_P1.27mm
U7: ESD2CAN24-Q1; SOT-23
U8: USBLC6-2SC6; SOT-23-6
U9: 74HCT14D; SOIC-14_3.9x8.7mm_P1.27mm
U10: E22-900M22S; Ebyte_E22-900M22S; not fitted
U11: 74LVC1G04; SOT-353_SC-70-5; not fitted
U12: LM66200DRLR; SOT-583-8
Y1: 25MHz ±30ppm; Crystal_SMD_3225-4Pin_3.2x2.5mm

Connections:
+3V3: C9.1, C10.1, C11.1, C12.1, C16.1, C26.1, C27.1, C31.1, C32.1, C33.1, C34.1, C35.1, C36.1, C37.1, C38.1, C39.1, J8.1, JP2.3 (B), JP3.1 (A), L1.2, R3.1, R15.1, R16.1, R17.1, R18.1, R20.2, R21.2, R24.1, R33.1, R34.1, R35.1, R36.1, R37.1, R38.1, R41.1, R42.1, R46.1, R51.1, R52.1, TP3.1 (1_1), U4.2 (3V3), U5.4 (AVDD), U5.8 (AVDD), U5.11 (AVDD), U5.15 (AVDD), U5.17 (AVDD), U5.21 (AVDD), U5.28 (VDD)
+3V3_LORA: C51.1, C52.1, R46.2, U10.9 (VCC), U11.5 (VCC)
+5V: C13.1, C22.1, C23.1, C45.1, C46.1, D6.1 (VDD), JP2.1 (A), R10.1, R44.1, TP2.1 (1_1), U3.3 (IN), U3.4 (IN), U9.14 (VCC), U12.2 (VOUT), U12.7 (VOUT)
+5V_BUCK: C56.1, C57.1, C58.1, C59.1, D10.1 (K), L3.2, R54.1, U12.3 (VIN1)
+24V_IN: F1.1, J1.1
+24V_P: C1.1, C2.1, C53.1, D2.1 (K), D8.2 (A), F1.2, R1.1, R56.1, TP1.1 (1_1), U2.2 (VIN), U2.3 (EN)
/BOOT: J5.6, R16.2, SW2.1, U4.15 (GPIO9)
/CAN_H: J2.4, J3.4, JP1.1 (A), JP4.2 (B), L2.2, TP5.1 (1_1), U7.2 (K)
/CAN_H_T: JP4.1 (A), L2.1, U6.7 (CANH)
/CAN_L: J2.3, J3.3, JP5.2 (B), L2.4, R25.2, TP6.1 (1_1), U7.1 (K)
/CAN_L_T: JP5.1 (A), L2.3, U6.6 (CANL)
/CAN_RX: U4.17 (GPIO19), U6.4 (RXD)
/CAN_TX: R35.2, U4.16 (GPIO18), U6.1 (TXD)
/CHIP_EN: C15.1, J5.5, R15.2, SW1.1, U4.3 (EN/CHIP_PU)
/ETH_CGND: C20.1, J6.8, J6.SH
/ETH_LED_ACT: J6.11, U5.27 (ACTLED)
/ETH_LED_LINK: J6.10, U5.25 (LINKLED)
/ETH_RCT: C17.1, J6.5 (RCT), R22.2, R23.2
/ETH_RXN_W: C61.1, R23.1, U5.5 (RXN)
/ETH_RXP_W: C19.1, R22.1, U5.6 (RXP)
/ETH_TXN: J6.2 (TD-), R21.1, U5.1 (TXN)
/ETH_TXP: J6.1 (TD+), R20.1, U5.2 (TXP)
/EXP_GPIO5: J8.2, R52.2, R53.1, U4.5 (MTDI/GPIO5/ADC1_CH5)
/GND_IN: J1.2, Q1.2 (D)
/GPIO15: R18.2, U4.23 (GPIO15)
/LORA_BUSY: U4.21 (GPIO23), U10.14 (BUSY)
/LORA_CS: R51.2, U4.20 (GPIO22), U10.19 (NSS)
/LORA_DIO1: U4.4 (MTMS/GPIO4/ADC1_CH4), U10.13 (DIO1)
/LORA_DIO2: U10.7 (TXEN), U10.8 (DIO2), U11.2
/LORA_RXEN: U10.6 (RXEN), U11.4
/PMODE0: R48.1, U5.45 (PMODE0)
/PMODE1: R49.1, U5.44 (PMODE1)
/PMODE2: R50.1, U5.43 (PMODE2)
/RGB_DIN_3V3: R17.2, R32.1, U4.10 (GPIO8), U9.1
/SPI_MISO: U4.27 (GPIO2/ADC1_CH2), U5.34 (MISO), U10.16 (MISO)
/SPI_MOSI: U4.7 (MTDO/GPIO7), U5.35 (MOSI), U10.17 (MOSI)
/SPI_SCLK: C28.1, R19.2, U5.33 (SCLK), U10.18 (SCK)
/U0RXD: J5.4, U4.24 (U0RXD/GPIO17)
/U0TXD: J5.3, R39.2
/USB_DM: C50.1, R27.2, U4.13 (GPIO12/USB_D-)
/USB_DM_CONN: J4.A7 (D-), J4.B7 (D-), R27.1, U8.3 (I/O2), U8.4 (I/O2)
/USB_DP: C49.1, R26.2, U4.14 (GPIO13/USB_D+)
/USB_DP_CONN: J4.A6 (D+), J4.B6 (D+), R26.1, U8.1 (I/O1), U8.6 (I/O1)
/VBUS_EN: D9.1 (K), U4.18 (GPIO20)
/VBUS_FAULT: R34.2, U3.6 (~FLT), U4.19 (GPIO21)
/VBUS_SENSE: C14.1, R13.2, R14.1, U4.9 (GPIO1/ADC1_CH1/XTAL_32K_N)
/VIN_SENSE: C3.1, R1.2, R2.1, U4.8 (GPIO0/ADC1_CH0/XTAL_32K_P)
/W5500_CS: R36.2, U4.11 (GPIO10), U5.32 (~SCS)
/W5500_INT: R38.2, U4.26 (GPIO3/ADC1_CH3), U5.36 (~INT)
/W5500_RST: R37.2, U4.12 (GPIO11), U5.37 (~RST), U10.15 (NRST)
CAN_VCC: C42.1, C43.1, JP2.2 (C), U6.3 (VDD)
CAN_VIO: C44.1, JP3.2 (C), U6.5 (Vio)
unnamed: D5.2 (A), R44.2
unnamed: D6.4 (DIN), R32.2, U9.4
unnamed: D9.2 (A), R10.2, R11.1, U3.2 (EN/UVLO)
unnamed: D12.1 (K), Q1.1 (G), R56.2
unnamed: J4.A5 (CC1), R28.1
unnamed: J4.B5 (CC2), R29.1
unnamed: J5.1, R33.2
unnamed: J6.9, R41.2
unnamed: J6.12, R42.2
unnamed: C19.2, J6.3 (RD+)
unnamed: C61.2, J6.6 (RD-)
unnamed: C18.1, J6.4 (TCT), R24.2
unnamed: J7.1 (In), U10.21 (ANT)
unnamed: JP1.2 (B), R25.1
unnamed: C7.1, U1.4 (BOOT)
unnamed: C9.2, R3.2, R4.1, U1.7 (FB)
unnamed: C7.2, L1.1, U1.3 (NC), U1.12 (SW)
unnamed: C8.1, U1.5 (VCC)
unnamed: C55.1, U2.7 (BOOT)
unnamed: R54.2, R55.1, U2.5 (FB)
unnamed: C55.2, L3.1, U2.8 (SW)
unnamed: C54.1, U2.6 (VCC)
unnamed: R12.1, U3.7 (ILM)
unnamed: C60.1, U3.1 (dVdt)
unnamed: R19.1, U4.6 (MTCK/GPIO6/ADC1_CH6)
unnamed: R39.1, U4.25 (U0TXD/GPIO16)
unnamed: R40.1, U5.10 (EXRES1)
unnamed: C29.1, U5.20 (TOCAP)
unnamed: C40.1, R47.1, U5.30 (XI/CLKIN), Y1.1
unnamed: C41.1, R47.2, U5.31 (XO), Y1.3
unnamed: R43.1, U6.8 (STBY)
unnamed: U9.2, U9.3
VIN_BUCK: C4.1, C5.1, C6.1, D3.1 (K), D8.1 (K), U1.2 (VIN), U1.9 (EN), U1.10 (VIN)
VUSB: C21.1, D3.2 (A), D11.1 (K), J4.A4 (VBUS), J4.A9 (VBUS), J4.B4 (VBUS), J4.B9 (VBUS), R30.1, U8.5 (VBUS), U12.6 (VIN2)
V_BUS: C24.1, C25.1, D4.1 (K), J2.1, J3.1, R13.1, TP4.1 (1_1), U3.5 (OUT)

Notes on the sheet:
L2: CAN-fojtó helye (üres), a JP4/JP5 áthidalja; fojtóval átvágni
9. BŐVÍTŐ (J8, GPIO5 = ADC1_CH5): 1-wire / gomb / revízió-osztó
felhúzások (10 k): GPIO8 · BOOT · CS · RST · GPIO15 · CAN_TX
3,3 V – U1 LMR36015BRNXR (1 MHz, L1 6,8 µH), VQFN-HR (RNX0012B)
VBUS_SENSE: 5 V → 0,9 V (GPIO1)
J5: 1 VREF · 2 GND · 3 TX · 4 RX · 5 EN · 6 BOOT
8. LoRa – U10 Ebyte E22-900M22S (SX1262, 868 MHz) + J7 u.FL – MINDEN DNP, később beültethető
Központi 5 V a buszra (2 A); USB-ről is: az U12 a nagyobbat választja (buck 5,2 V > USB). A C1 elkó kötelező; a tápot ≤ 26 V-ra (az U2 max. 36 V)
W5500 PMODE-lehúzás (DNP)
7. LED-EK, RGB, DEBUG – U9 és R32 egyszerre NE legyen beültetve
VBG (18) NYITVA · RSVD 38–42 NYITVA · RSVD 23 GND · PMODE nyitva = auto-negotiation (R48–R50 lehúzás DNP)
5. USB-C – csak eszköz, csak táp-fogyasztó
6. CAN – U6 TCAN1044AVDRQ1 (MCP2562 szimbólum, lábról lábra azonos) · JP2 alap 5 V: 1044/2562 · 3V3: 330/230
CC1/CC2 külön 5,1 kΩ; USBLC6 az aljzatnál, 22 Ω a C6-nál
4. ETHERNET – U5 W5500 + J6 HR911105A MagJack (opcionálisan beültetve; MDI a WIZnet use_mag referencia szerint)
W5500 hidegítés: AVDD-lábanként 100 nF + 10 µF a +3V3-ról
MDI (WIZnet-referencia): TX 49,9 Ω a +3V3-ra; RX 49,9 Ω → RCT + 10 nF; RX-ben soros 6,8 nF
ESD (U7) · lezárás: JP1 + R25 (csak a lánc végén)
3. ESP32-C6-WROOM-1-N8 (fém szekrénybe -1U ugyanerre a footprintre) – strapping: GPIO8 = 1, GPIO9 = 1 (BOOT gomb → 0), GPIO15 · RESET és BOOT gomb a lábánál
2. V_BUS – U3 TPS259531 eFuse: 2 A-es korlát, 5,7 V-os túlfeszültség-vágás; EN-osztó a +5V-ról (bármelyik forrásról BE), a GPIO20 a D9-en (BAT54) át letiltja
1. TÁP (12–26 V): +24V_IN → F1 → +24V_P (Q1 a GND-ágban) → D8 → VIN_BUCK (U1 LMR36015 → 3,3 V); +24V_P → U2 LMR33630 (5,2 V) → U12 LM66200 → +5V
SPI a W5500-zal közös; NRST = W5500_RST (közös reset); TXEN = DIO2, RXEN = ¬DIO2 (U11) → firmware: setDio2AsRfSwitch
RGB_DIN

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
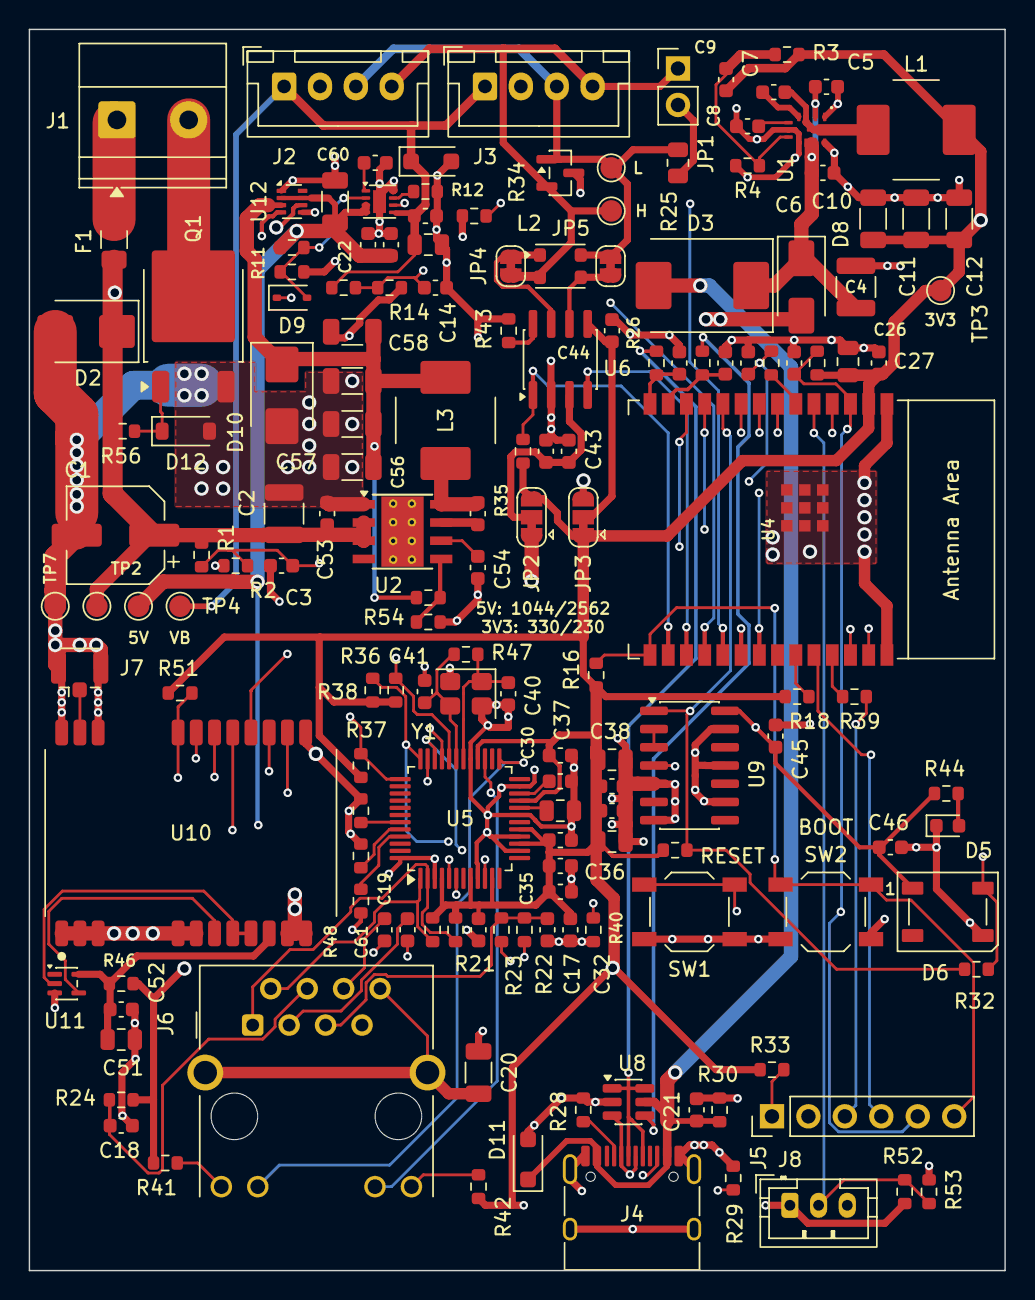
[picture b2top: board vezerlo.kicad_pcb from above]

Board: 4 copper layers, 68.0 x 86.5 mm, 158 parts (0 on the bottom side), 89 nets.

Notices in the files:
parts and their libraries:
ESP32-C6-WROOM-1/U is a module that supports 2.4 GHz Wi-Fi 6 (802.11 ax), Bluetooth® 5 (LE), Zigbee and Thread (802.15.4) – Forrás: espressif/kicad-libraries (CC-BY-SA 4.0 + KiCad-kivétel).
